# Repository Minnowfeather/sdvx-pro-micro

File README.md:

# DJDao Arduino Drop-in Replacement

This project aims to be a drop-in replacement for DJDao SVSE5 and SVRE9 PCBs. Currently only supports potentiometers and DJDao-style wiring.

LEDs are wired to 5V and a GPIO pin on the Pro Micro. Writing LOW will turn ON the LED, and writing HIGH will turn it OFF. If your LEDs don't turn on, try flipping them around.

# Pin assignments

| Button | Data | LED |
| ------ | ---- | --- |
| BT-A   | 2    | 3   |
| BT-B   | 4    | 5   |
| BT-C   | 6    | 7   |
| BT-D   | 10   | 16  |
| FX-L   | 14   | 15  |
| FX-R   | A0   | A1  |
| Start  | 1    | 0   |
| VOL-L  | A2   | N/A |
| VOL-R  | A3   | N/A |

# Code

Use a modifed version of [KnucklesLee&#39;s code](https://github.com/knuckleslee/RhythmCodes/).

# Known Issues

V1: Pots are jittery, affected by the LEDs, and each other(?)
V1: Button pins have swapped GND and 5V

V2: Pots are a bit jittery when using a 0.1μF capacitor. Possibly fixed with higher value cap?
V2: Pro Micro footprint is actually a Teensy 2.0 footprint. This is only a cosmetic difference.
V2: Pro Micro USB-C slot is blocked by the Start button, requiring it to be mounted upside-down
V2: Upside-down mounting might require extension cables for each button

# ToDO

- Add pins for a reset button
- Replace Teensy footprint with Pro Micro footprint
- Add quadrature encoder support
- Add firmware code

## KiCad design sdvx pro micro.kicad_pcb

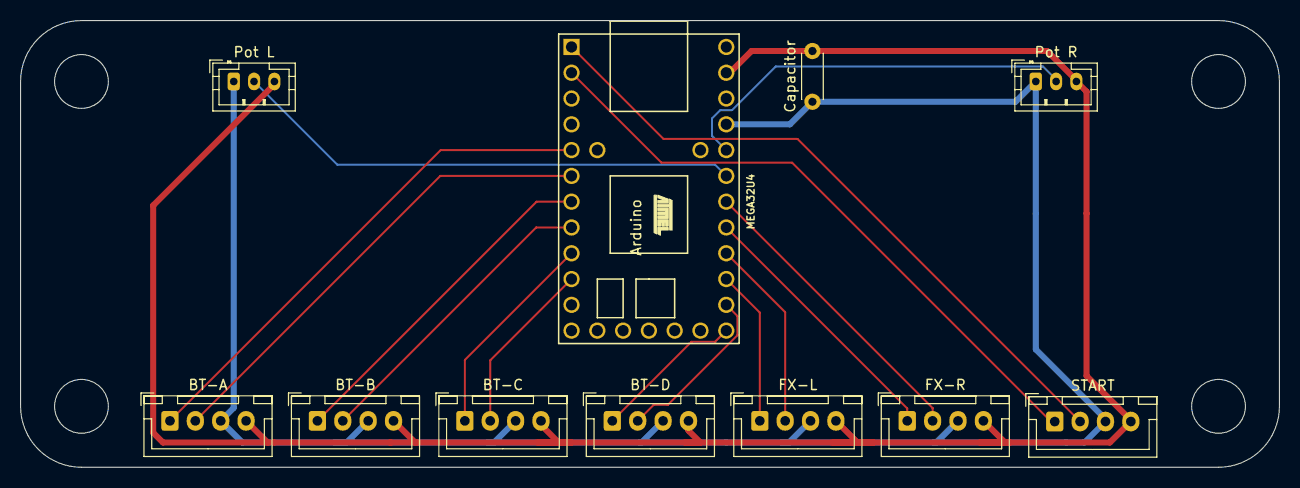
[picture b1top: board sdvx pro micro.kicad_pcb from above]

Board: 2 copper layers, 124.0 x 44.0 mm, 11 parts (0 on the bottom side), 5 nets.

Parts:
Arduino: Teensy2.0
BT-A: JST_XH_B4B-XH-A_1x04_P2.50mm_Vertical
BT-B: JST_XH_B4B-XH-A_1x04_P2.50mm_Vertical
BT-C: JST_XH_B4B-XH-A_1x04_P2.50mm_Vertical
BT-D: JST_XH_B4B-XH-A_1x04_P2.50mm_Vertical
Capacitor: C_Disc_D4.3mm_W1.9mm_P5.00mm
FX-L: JST_XH_B4B-XH-A_1x04_P2.50mm_Vertical
FX-R: JST_XH_B4B-XH-A_1x04_P2.50mm_Vertical
Pot L: JST_PH_B3B-PH-K_1x03_P2.00mm_Vertical
Pot R: JST_PH_B3B-PH-K_1x03_P2.00mm_Vertical
START: JST_XH_B4B-XH-A_1x04_P2.50mm_Vertical

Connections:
5V: Arduino.26, BT-A.3, BT-B.3, BT-C.3, BT-D.3, Capacitor.1, FX-L.3, FX-R.3, Pot L.1, Pot R.1, START.3
ButtonData: Arduino.2, Arduino.5, Arduino.7, Arduino.9, Arduino.18, Arduino.20, Arduino.22, BT-A.1, BT-B.1, BT-C.1, BT-D.1, FX-L.1, FX-R.1, START.1
EncData: Arduino.24, Arduino.25, Pot L.2, Pot R.2
Ground: Arduino.3, Arduino.4, Arduino.28, BT-A.4, BT-B.4, BT-C.4, BT-D.4, Capacitor.2, FX-L.4, FX-R.4, Pot L.3, Pot R.3, START.4
LightData: Arduino.1, Arduino.6, Arduino.8, Arduino.10, Arduino.19, Arduino.21, Arduino.23, BT-A.2, BT-B.2, BT-C.2, BT-D.2, FX-L.2, FX-R.2, START.2

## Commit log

2025-06-08 V1 upload
2025-06-12 added capacitor to 5V line to reduce capacitor noise. swapped JST-ZH for JST-PH
2025-06-12 swapped JST-ZH for PH, added capacitor to stabilize pots
2025-06-12 Added README, updated gitignore
2025-06-12 Increased GND track width, moved capacitor closer to VCC
